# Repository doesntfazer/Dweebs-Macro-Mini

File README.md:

# Dweebs-Macro-Mini
Macro Pad for gaming

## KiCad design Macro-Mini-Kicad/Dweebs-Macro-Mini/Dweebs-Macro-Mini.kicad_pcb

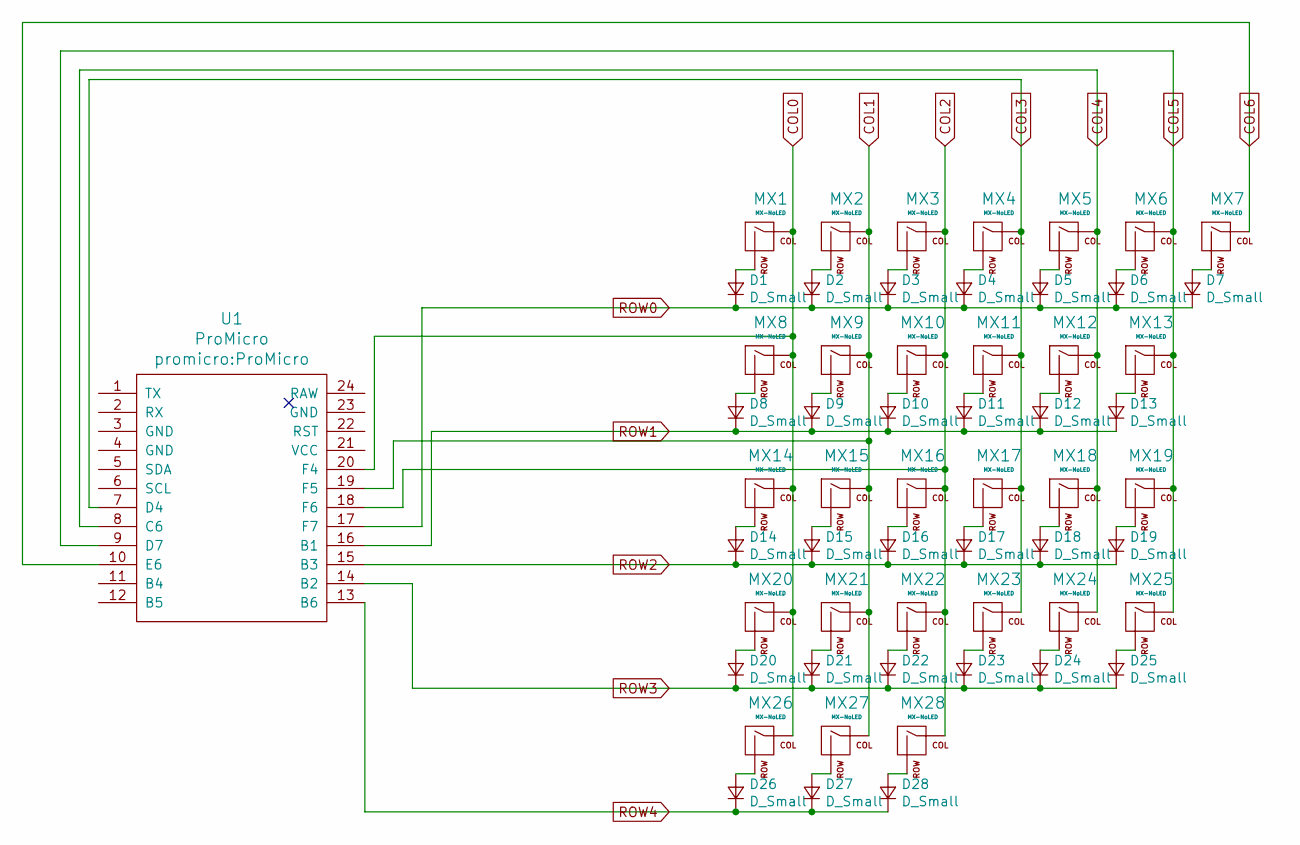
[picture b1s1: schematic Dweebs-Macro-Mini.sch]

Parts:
D1, D2, D3, D4, D5, D6, D7, D8, D9, D10, D11, D12, D13, D14, D15, D16, D17, D18, D19, D20, D21, D22, D23, D24, D25, D26, D27, D28: D_Small; D_SOD-123
MX1, MX2, MX3, MX4, MX5, MX6, MX7, MX8, MX9, MX10, MX11, MX12, MX13, MX14, MX15, MX16, MX17, MX18, MX19, MX20, MX21, MX22, MX23, MX24, MX25, MX26, MX27, MX28: MX-NoLED; MX-1U-NoLED
U1: ProMicro

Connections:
COL0: MX1.1 (COL), MX8.1 (COL), MX14.1 (COL), MX20.1 (COL), MX26.1 (COL), U1.20 (F4)
COL1: MX2.1 (COL), MX9.1 (COL), MX15.1 (COL), MX21.1 (COL), MX27.1 (COL), U1.19 (F5)
COL2: MX3.1 (COL), MX10.1 (COL), MX16.1 (COL), MX22.1 (COL), MX28.1 (COL), U1.18 (F6)
COL3: MX4.1 (COL), MX11.1 (COL), MX17.1 (COL), MX23.1 (COL), U1.7 (D4)
COL4: MX5.1 (COL), MX12.1 (COL), MX18.1 (COL), MX24.1 (COL), U1.8 (C6)
COL5: MX6.1 (COL), MX13.1 (COL), MX19.1 (COL), MX25.1 (COL), U1.9 (D7)
COL6: MX7.1 (COL), U1.10 (E6)
unnamed: D1.2 (A), MX1.2 (ROW)
unnamed: D2.2 (A), MX2.2 (ROW)
unnamed: D3.2 (A), MX3.2 (ROW)
unnamed: D4.2 (A), MX4.2 (ROW)
unnamed: D5.2 (A), MX5.2 (ROW)
unnamed: D6.2 (A), MX6.2 (ROW)
unnamed: D7.2 (A), MX7.2 (ROW)
unnamed: D8.2 (A), MX8.2 (ROW)
unnamed: D9.2 (A), MX9.2 (ROW)
unnamed: D10.2 (A), MX10.2 (ROW)
unnamed: D11.2 (A), MX11.2 (ROW)
unnamed: D12.2 (A), MX12.2 (ROW)
unnamed: D13.2 (A), MX13.2 (ROW)
unnamed: D14.2 (A), MX14.2 (ROW)
unnamed: D15.2 (A), MX15.2 (ROW)
unnamed: D16.2 (A), MX16.2 (ROW)
unnamed: D17.2 (A), MX17.2 (ROW)
unnamed: D18.2 (A), MX18.2 (ROW)
unnamed: D19.2 (A), MX19.2 (ROW)
unnamed: D20.2 (A), MX20.2 (ROW)
unnamed: D21.2 (A), MX21.2 (ROW)
unnamed: D22.2 (A), MX22.2 (ROW)
unnamed: D23.2 (A), MX23.2 (ROW)
unnamed: D24.2 (A), MX24.2 (ROW)
unnamed: D25.2 (A), MX25.2 (ROW)
unnamed: D26.2 (A), MX26.2 (ROW)
unnamed: D27.2 (A), MX27.2 (ROW)
unnamed: D28.2 (A), MX28.2 (ROW)
ROW0: D1.1 (K), D2.1 (K), D3.1 (K), D4.1 (K), D5.1 (K), D6.1 (K), D7.1 (K), U1.17 (F7)
ROW1: D8.1 (K), D9.1 (K), D10.1 (K), D11.1 (K), D12.1 (K), D13.1 (K), U1.16 (B1)
ROW2: D14.1 (K), D15.1 (K), D16.1 (K), D17.1 (K), D18.1 (K), D19.1 (K), U1.15 (B3)
ROW3: D20.1 (K), D21.1 (K), D22.1 (K), D23.1 (K), D24.1 (K), D25.1 (K), U1.14 (B2)
ROW4: D26.1 (K), D27.1 (K), D28.1 (K), U1.13 (B6)

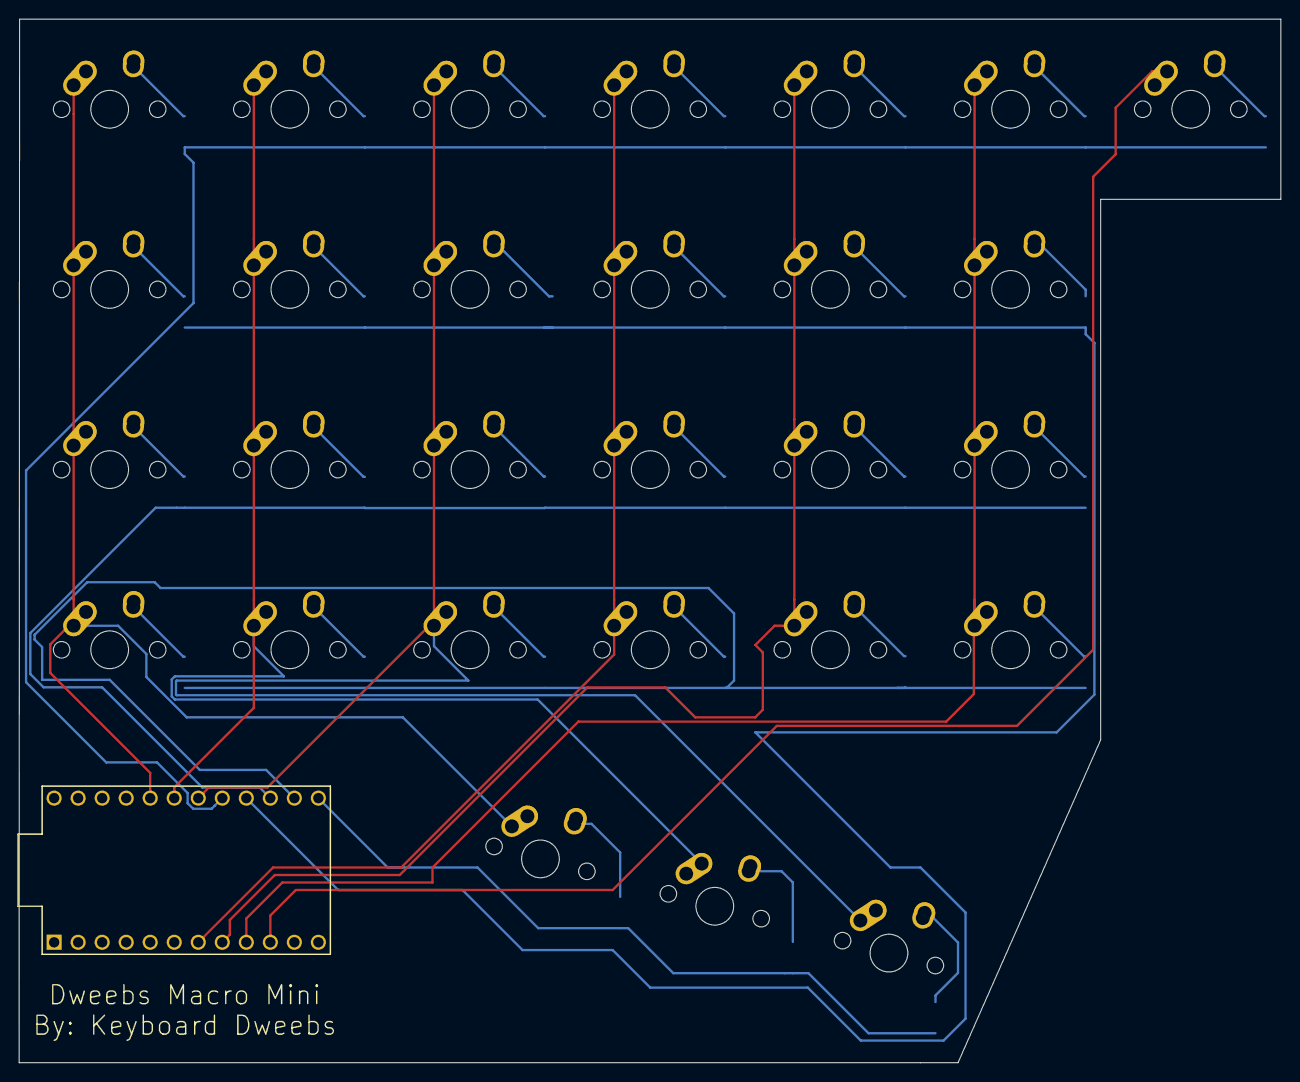
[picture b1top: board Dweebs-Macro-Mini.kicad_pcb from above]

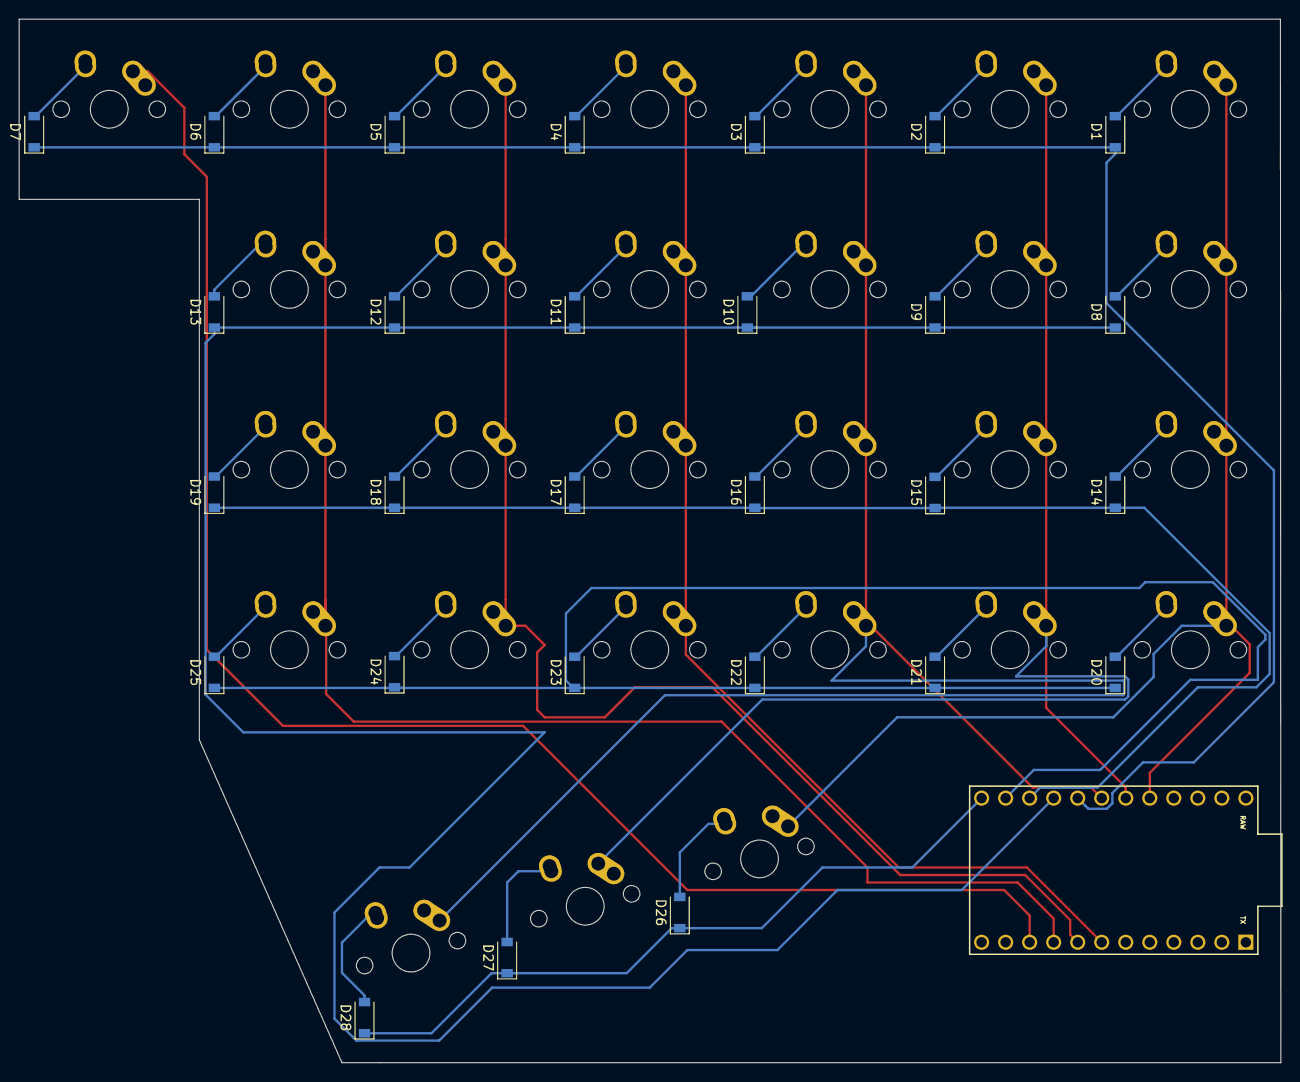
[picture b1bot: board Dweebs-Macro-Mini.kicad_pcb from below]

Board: 2 copper layers, 133.4 x 110.3 mm, 57 parts (28 on the bottom side), 40 nets.

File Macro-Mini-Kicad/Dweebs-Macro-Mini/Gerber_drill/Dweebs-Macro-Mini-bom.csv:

"Id";"Designator";"Package";"Quantity";"Designation";"Supplier and ref";
1;"REF**,REF**,REF**,REF**,REF**";"M2_Hole_TH_Outside";5;"M2_Hole_TH_Outside";;;
2;"MX20,MX28,MX27,MX26,MX25,MX24,MX23,MX22,MX21,MX19,MX18,MX17,MX16,MX15,MX14,MX13,MX12,MX11,MX10,MX9,MX8,MX7,MX6,MX5,MX4,MX3,MX2,MX1";"MX-1U-NoLED";28;"MX-NoLED";;;
3;"U1";"ProMicro";1;"ProMicro";;;
4;"D28,D27,D26,D25,D24,D23,D22,D21,D20,D19,D18,D17,D16,D15,D14,D13,D12,D11,D10,D9,D8,D7,D6,D5,D4,D3,D2,D1";"D_SOD-123";28;"D_Small";;;

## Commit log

2022-03-13 Adding case files
    Adding case files
2022-03-13 initial pcb files
    Not gonna work yet
2022-03-13 footprint libraries
2022-03-13 tables
2022-03-14 routes done
2022-03-14 Final for proto
2022-03-14 remade vias
2022-03-14 trace reroute
2022-03-14 silkscreen
2022-03-14 gerbers
2022-03-14 adjust
2022-03-14 updated cut to match vector
2022-03-14 made changes to gerber
2022-03-14 Update Dweebs-Macro-Mini.kicad_pcb-bak
2022-03-17 added mount holes and fr4 board
2022-03-17 file restructure
2022-03-17 more crap
2022-03-18 change
2022-03-29 case files
